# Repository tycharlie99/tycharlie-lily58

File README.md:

# Lily58 - Wireless

An ergonomic, split mechanical keyboard with a 58-key columnar-staggered layout, derived from the original [Lily58](https://github.com/kata0510/Lily58). This specific variant is optimized for wireless dual-mode connectivity and ultra-low-power Nice!View displays, perfect for developers and creators seeking a clean, cable-free workspace.

## Features

- **Ergonomic Columnar Layout**: 4x12 matrix with 5 thumb keys per side (58 keys total) reduces finger travel and hand strain.
- **Wireless-Ready**: Integrated battery support for seamless Bluetooth operation when paired with BLE controllers (e.g., nice!nano).
- **Nice!View Optimization**: Native compatibility with the low-power Sharp Memory Display (Nice!View), offering a high refresh rate with a fraction of the power consumption of traditional OLEDs.
- **Reversible PCB Design**: Uses a mirrored, flippable design for the left and right sides to simplify manufacturing and sourcing.
---

## Bill of Materials (BOM)

Below is the complete list of components required to build one full TsunyYu - Lily58 keyboard (including both left and right halves):

| Item | Quantity | Model/Specification / Notes |
| --- | --- | --- |
| **Lily58 PCB** | 2 | Left and right halves (reversible design) |
| **PCB Plate** | 2 | Left and right halves (compatible with 58-key layout) |
| **Microcontroller** | 2 | Pro Micro or compatible BLE wireless controllers (e.g., nice!nano) |
| **Tulip Socket** | 2 | SINGLE STRIP ROW 40 CONTACTS, PITCH = 2.54mm |
| **Machined Pin Header** | 2 | Single row 30 contacts, 2.54mm Round Pin Header |
| **Display** | 2 | Nice!View (Ultra-low-power display; backward compatible with 0.91" OLED) |
| **Square Pin Socket** | 2 | 1x5 Female Header |
| **M2 Screw** | 10 | M2x6mm |
| **M2 Spacer** | 10 | |
| **Key Socket** | 58 | Kailh Hotswap Sockets |
| **Switches** | 58 | MX switches |
| **Keycaps** | 58 | 1U keycaps recommended, 1.5U (2) optional for thumb keys |
| **Diodes** | 58 | 1N4148W (SOD-123) |
| **Batteries** | 2 | 3.7V Li-Po batteries (Required for wireless; 110mAh to 300mAh recommended) |
| **Battery Holders** | 2 | Molex 53621-0271 1.25mm 2p |
| **Reset Buttons** | 2 | C&K PTS636 SMT G leads 2.5mm height |

---

## Hardware & Soldering Guide

Please review these critical steps before heating up your soldering iron:

1. **Orientation Check**: Because the PCB is reversible, make sure you clearly identify the "Left" and "Right" sides before soldering any components. Do not accidentally mirror the components on the same side.
2. **Diode Polarity**: Diodes are directional. Ensure the line on the diode (cathode) aligns with the thick line/bar indicated on the PCB silkscreen markings.
3. **Wireless Safety Precautions**:
   - It is highly recommended to apply **insulating tape** (like Kapton tape) over the PCB traces beneath the microcontroller to prevent shorts between the controller pins and the PCB components/battery.
   - Pay close attention to the pinout when installing the Nice!View. It requires 5 pins (including a CS pin), differing slightly from standard 4-pin OLED setups.

---

## Firmware Support

This build is fully compatible with open-source keyboard firmwares:

- **ZMK Firmware**: The ideal choice when paired with nice!nano controllers. It natively handles Bluetooth multi-device pairing and unlocks the full low-power efficiency of the Nice!View screen.

---

## References & Credits

This project is built upon and inspired by the incredible open-source work of the mechanical keyboard community:

- [kata0510/Lily58](https://github.com/kata0510/Lily58) - The original Lily58 design.
- [ZMK Firmware](https://zmk.dev/) & [nice!nano](https://nicekeyboards.com/) - Providing the robust ecosystem for wireless split keyboards.

---

## License

This hardware project is open-source and distributed under the same licensing terms as the original repository:
- **Distributed under the [MIT License](LICENSE)** *(Or specify CERN OHL if applicable to your custom PCB modifications).*

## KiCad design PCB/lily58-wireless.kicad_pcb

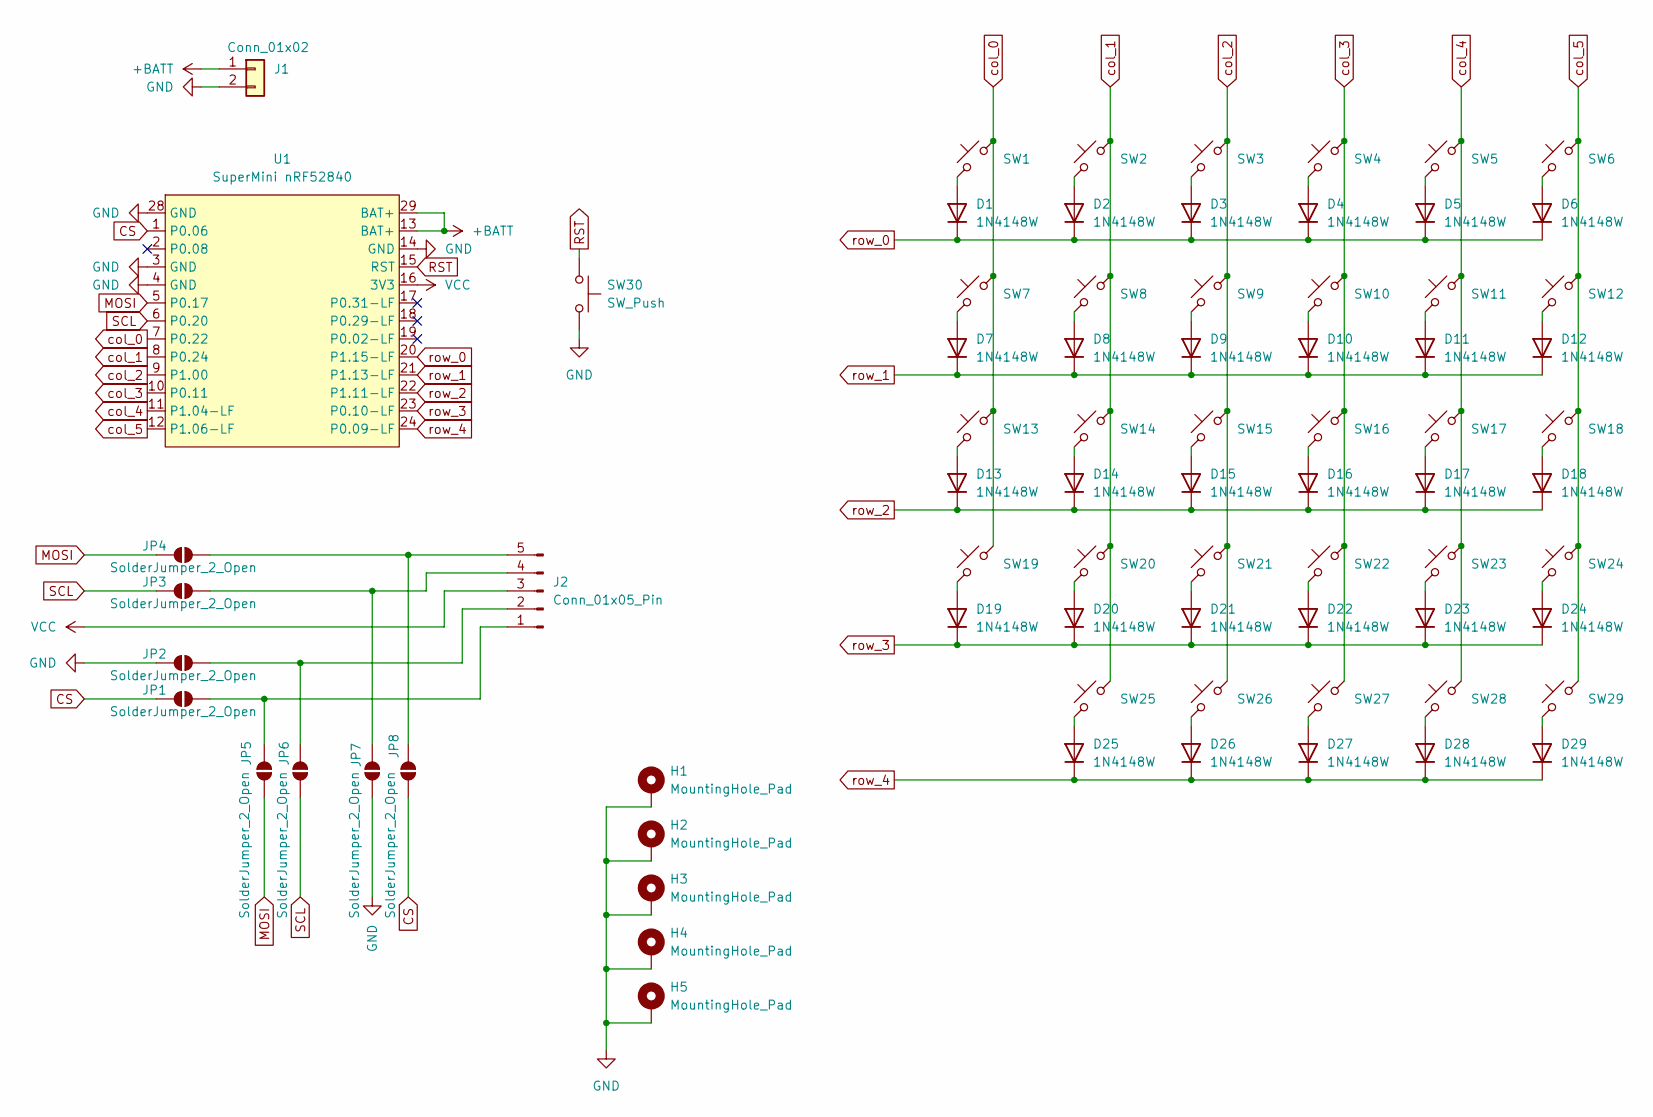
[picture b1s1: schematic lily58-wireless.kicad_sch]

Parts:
D1, D2, D3, D4, D5, D6, D7, D8, D9, D10, D11, D12, D13, D14, D15, D16, D17, D18, D19, D20, D21, D22, D23, D24, D25, D26, D27, D28, D29: 1N4148W; D_SOD-123
H1, H2, H4, H5: MountingHole_Pad; MountingHole_3mm_Oval_Pad_TopBottom
H3: MountingHole_Pad; MountingHole_2.2mm_Pad_TopBottom
J1: Conn_01x02; Molex_PicoBlade_53261-0271_1x02-1MP_P1.25mm_Horizontal
J2: Conn_01x05_Pin; PinHeader_1x05_P2.54mm_Vertical
JP1, JP2, JP3, JP4, JP5, JP6, JP7, JP8: SolderJumper_2_Open; SolderJumper-2_P1.3mm_Open_RoundedPad1.0x1.5mm
SW1, SW2, SW3, SW4, SW5, SW6, SW7, SW8, SW9, SW10, SW11, SW12, SW13, SW14, SW15, SW16, SW17, SW18, SW19, SW20, SW21, SW22, SW23, SW24, SW25, SW26, SW27, SW28, SW29: SW_Push_45deg; SW_Hotswap_Reversible_Kailh_MX_Plated_1.00u
SW30: SW_Push; SW_Tactile_SPST_NO_Straight_CK_PTS636Sx25SMTRLFS
U1: SuperMini nRF52840; SuperMini_nRF52840_without_25-27

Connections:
+BATT: J1.1, U1.13 (BAT+), U1.29 (BAT+)
CS: JP1.1 (A), JP8.1 (A), U1.1 (P0.06)
GND: H1.1 (1_1), H2.1 (1_1), H3.1 (1_1), H4.1 (1_1), H5.1 (1_1), J1.2, JP2.1 (A), JP7.1 (A), SW30.2, U1.3 (GND), U1.4 (GND), U1.14 (GND), U1.28 (GND)
MOSI: JP4.1 (A), JP5.1 (A), U1.5 (P0.17)
unnamed: D1.2 (A), SW1.1
unnamed: D2.2 (A), SW2.1
unnamed: D3.2 (A), SW3.1
unnamed: D4.2 (A), SW4.1
unnamed: D5.2 (A), SW5.1
unnamed: D6.2 (A), SW6.1
unnamed: D7.2 (A), SW7.1
unnamed: D8.2 (A), SW8.1
unnamed: D9.2 (A), SW9.1
unnamed: D10.2 (A), SW10.1
unnamed: D11.2 (A), SW11.1
unnamed: D12.2 (A), SW12.1
unnamed: D13.2 (A), SW13.1
unnamed: D14.2 (A), SW14.1
unnamed: D15.2 (A), SW15.1
unnamed: D16.2 (A), SW16.1
unnamed: D17.2 (A), SW17.1
unnamed: D18.2 (A), SW18.1
unnamed: D19.2 (A), SW19.1
unnamed: D20.2 (A), SW20.1
unnamed: D21.2 (A), SW21.1
unnamed: D22.2 (A), SW22.1
unnamed: D23.2 (A), SW23.1
unnamed: D24.2 (A), SW24.1
unnamed: D25.2 (A), SW25.1
unnamed: D26.2 (A), SW26.1
unnamed: D27.2 (A), SW27.1
unnamed: D28.2 (A), SW28.1
unnamed: D29.2 (A), SW29.1
unnamed: J2.1, JP1.2 (B), JP5.2 (B)
unnamed: J2.2, JP2.2 (B), JP6.2 (B)
unnamed: J2.4, JP3.2 (B), JP7.2 (B)
unnamed: J2.5, JP4.2 (B), JP8.2 (B)
RST: SW30.1, U1.15 (RST)
SCL: JP3.1 (A), JP6.1 (A), U1.6 (P0.20)
VCC: J2.3, U1.16 (3V3)
col_0: SW1.2, SW7.2, SW13.2, SW19.2, U1.7 (P0.22)
col_1: SW2.2, SW8.2, SW14.2, SW20.2, SW25.2, U1.8 (P0.24)
col_2: SW3.2, SW9.2, SW15.2, SW21.2, SW26.2, U1.9 (P1.00)
col_3: SW4.2, SW10.2, SW16.2, SW22.2, SW27.2, U1.10 (P0.11)
col_4: SW5.2, SW11.2, SW17.2, SW23.2, SW28.2, U1.11 (P1.04-LF)
col_5: SW6.2, SW12.2, SW18.2, SW24.2, SW29.2, U1.12 (P1.06-LF)
row_0: D1.1 (K), D2.1 (K), D3.1 (K), D4.1 (K), D5.1 (K), D6.1 (K), U1.20 (P1.15-LF)
row_1: D7.1 (K), D8.1 (K), D9.1 (K), D10.1 (K), D11.1 (K), D12.1 (K), U1.21 (P1.13-LF)
row_2: D13.1 (K), D14.1 (K), D15.1 (K), D16.1 (K), D17.1 (K), D18.1 (K), U1.22 (P1.11-LF)
row_3: D19.1 (K), D20.1 (K), D21.1 (K), D22.1 (K), D23.1 (K), D24.1 (K), U1.23 (P0.10-LF)
row_4: D25.1 (K), D26.1 (K), D27.1 (K), D28.1 (K), D29.1 (K), U1.24 (P0.09-LF)

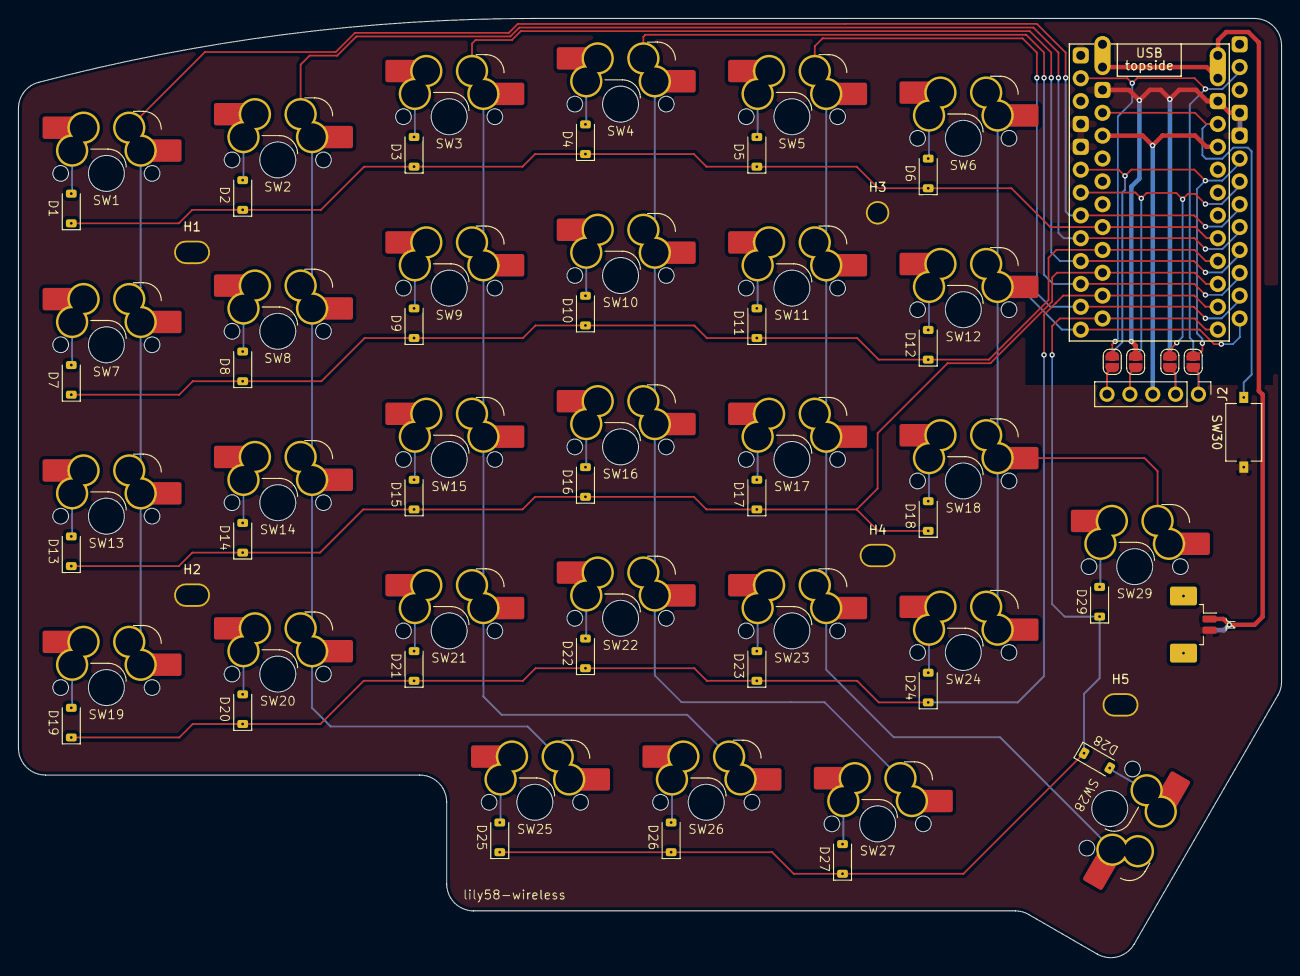
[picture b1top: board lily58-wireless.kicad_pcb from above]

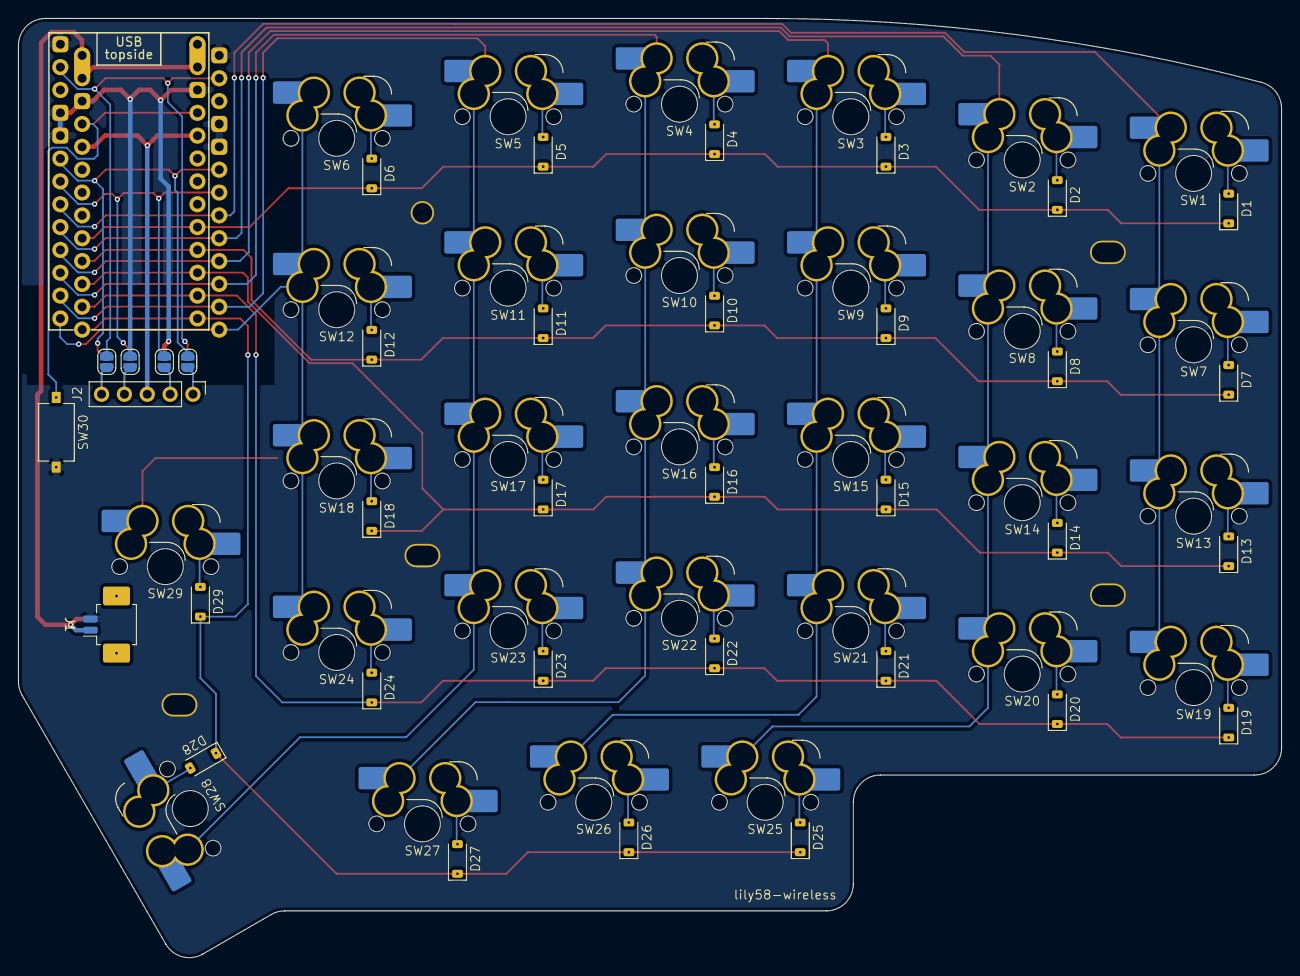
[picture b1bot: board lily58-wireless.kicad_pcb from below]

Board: 2 copper layers, 140.4 x 104.4 mm, 75 parts (34 on the bottom side), 51 nets.

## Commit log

2026-06-14 FEAT: remove the wire part keep the wireless part
    - rename the project to "lily58-wireless"
    - add project symbol library
    - redesing the plate pcb
    - change the screw hole to 5mm
    - update the reset push buttom
    - update the README
